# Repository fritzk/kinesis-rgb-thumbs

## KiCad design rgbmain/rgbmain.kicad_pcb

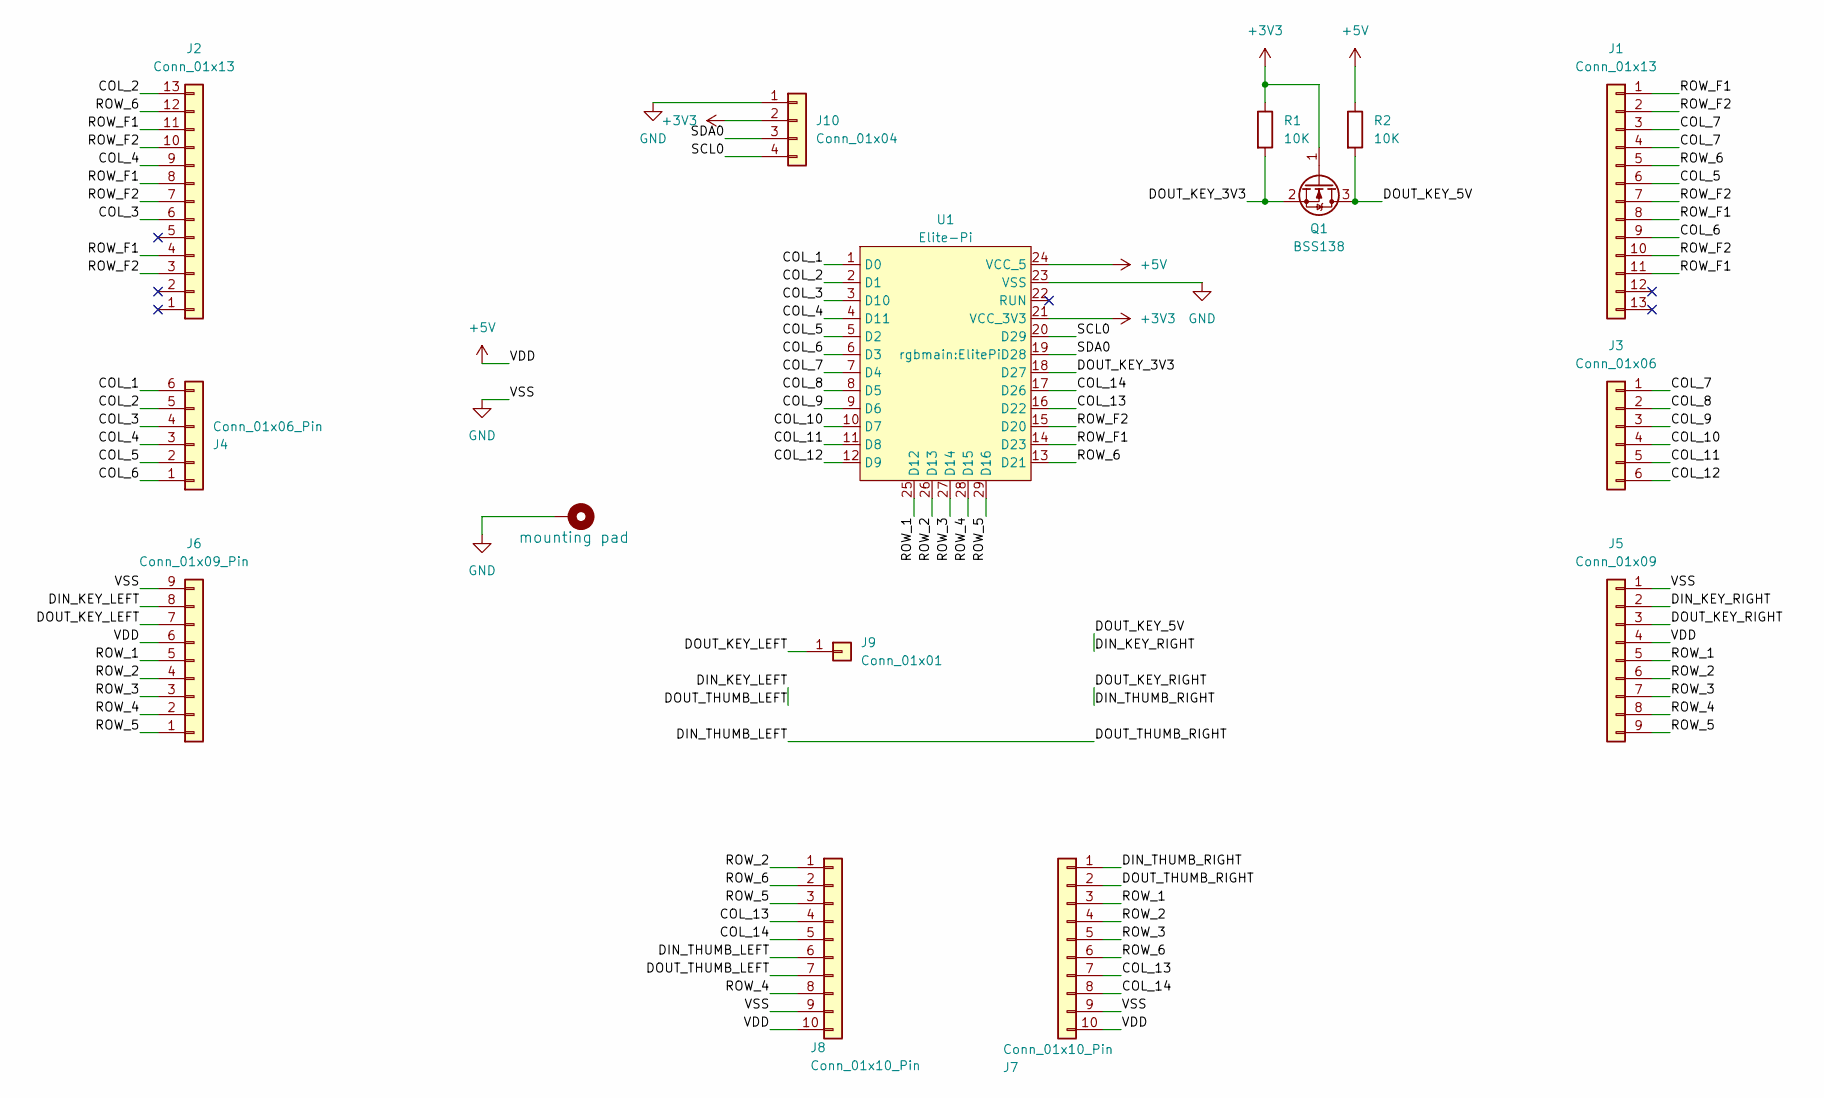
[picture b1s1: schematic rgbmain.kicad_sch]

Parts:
H1: mounting pad; MountingHole_4.3mm_M4_Pad
J1, J2: Conn_01x13; Molex_0039532135
J3: Conn_01x06; Molex_KK-254_AE-6410-06A_1x06_P2.54mm_Vertical
J4: Conn_01x06_Pin; Molex_KK-254_AE-6410-06A_1x06_P2.54mm_Vertical
J5: Conn_01x09; Molex_KK-254_AE-6410-09A_1x09_P2.54mm_Vertical
J6: Conn_01x09_Pin; Molex_KK-254_AE-6410-09A_1x09_P2.54mm_Vertical
J7, J8: Conn_01x10_Pin; PinHeader_1x10_P2.54mm_Vertical
J9: Conn_01x01; PinHeader_1x01_P1.00mm_Vertical
J10: Conn_01x04; PinSocket_1x04_P2.54mm_Vertical
Q1: BSS138; SOT-23
R1, R2: 10K; R_0805_2012Metric_Pad1.20x1.40mm_HandSolder
U1: Elite-Pi; ElitePi

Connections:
+3V3: J10.2, Q1.1 (G), R1.1, U1.21 (VCC_3V3)
+5V: J5.4, J6.6, J7.10, J8.10, R2.1, U1.24 (VCC_5)
/COL_1: J4.6, U1.1 (D0)
/COL_2: J2.13, J4.5, U1.2 (D1)
/COL_3: J2.6, J4.4, U1.3 (D10)
/COL_4: J2.9, J4.3, U1.4 (D11)
/COL_5: J1.6, J4.2, U1.5 (D2)
/COL_6: J1.9, J4.1, U1.6 (D3)
/COL_7: J1.3, J1.4, J3.1, U1.7 (D4)
/COL_8: J3.2, U1.8 (D5)
/COL_9: J3.3, U1.9 (D6)
/COL_10: J3.4, U1.10 (D7)
/COL_11: J3.5, U1.11 (D8)
/COL_12: J3.6, U1.12 (D9)
/COL_13: J7.7, J8.4, U1.16 (D22)
/COL_14: J7.8, J8.5, U1.17 (D26)
/DIN_KEY_LEFT: J6.8, J8.7
/DIN_KEY_RIGHT: J5.2, Q1.3 (D), R2.2
/DIN_THUMB_LEFT: J7.2, J8.6
/DIN_THUMB_RIGHT: J5.3, J7.1
/DOUT_KEY_3V3: Q1.2 (S), R1.2, U1.18 (D27)
/DOUT_KEY_LEFT: J6.7, J9.1
/ROW_1: J5.5, J6.5, J7.3, U1.25 (D12)
/ROW_2: J5.6, J6.4, J7.4, J8.1, U1.26 (D13)
/ROW_3: J5.7, J6.3, J7.5, U1.27 (D14)
/ROW_4: J5.8, J6.2, J8.8, U1.28 (D15)
/ROW_5: J5.9, J6.1, J8.3, U1.29 (D16)
/ROW_6: J1.5, J2.12, J7.6, J8.2, U1.13 (D21)
/ROW_F1: J1.1, J1.8, J1.11, J2.4, J2.8, J2.11, U1.14 (D23)
/ROW_F2: J1.2, J1.7, J1.10, J2.3, J2.7, J2.10, U1.15 (D20)
/SCL0: J10.4, U1.20 (D29)
/SDA0: J10.3, U1.19 (D28)
GND: H1.1, J5.1, J6.9, J7.9, J8.9, J10.1, U1.23 (VSS)

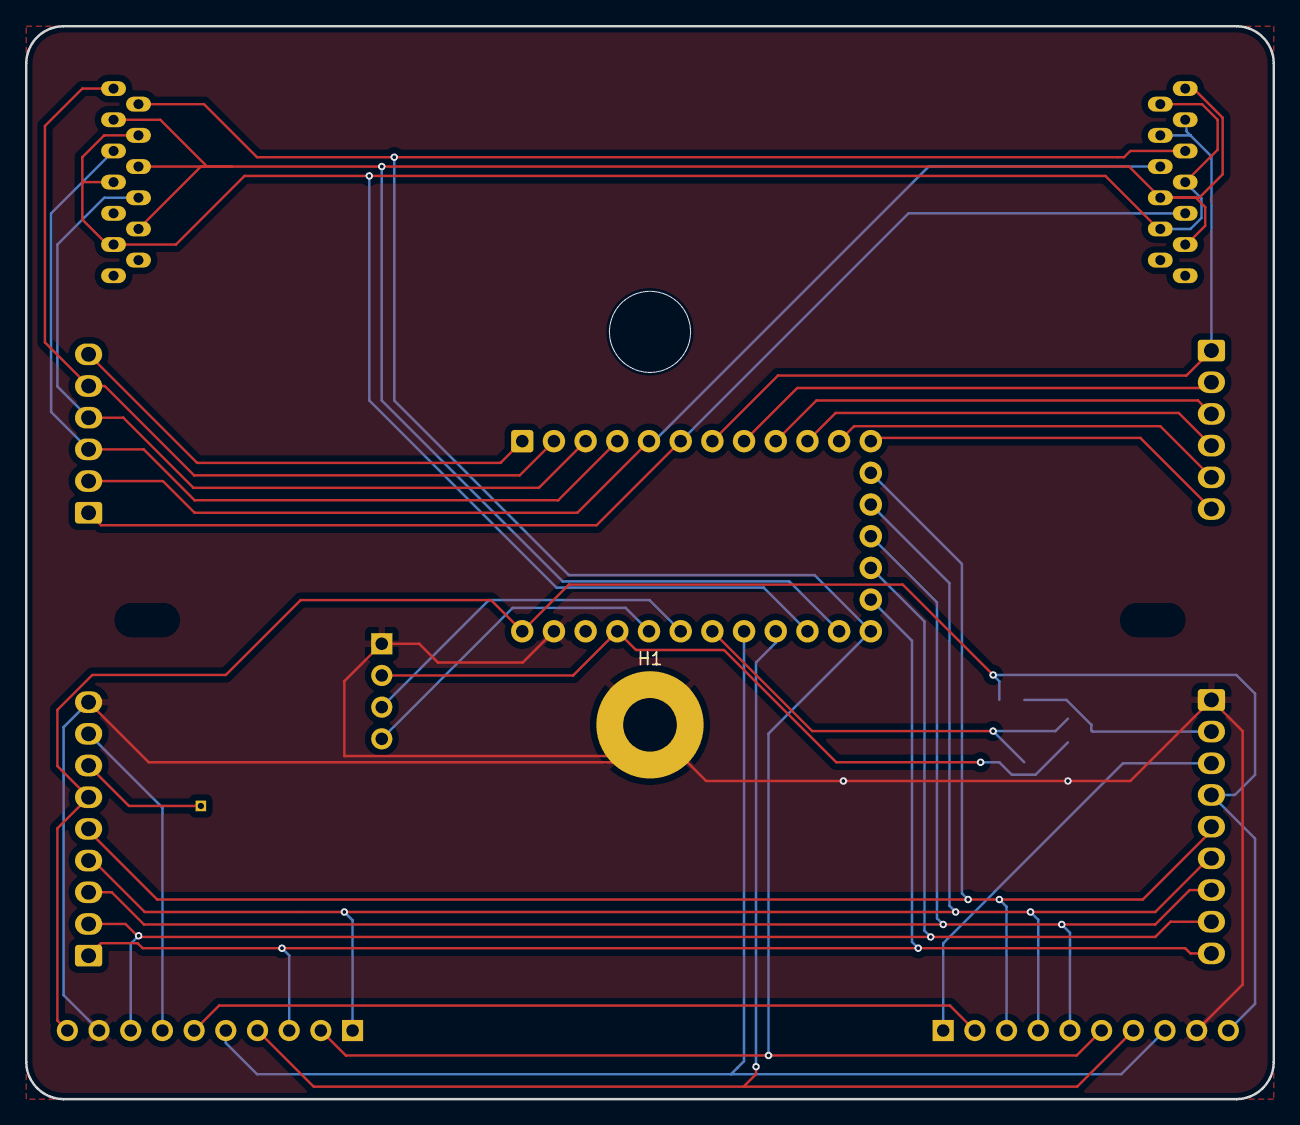
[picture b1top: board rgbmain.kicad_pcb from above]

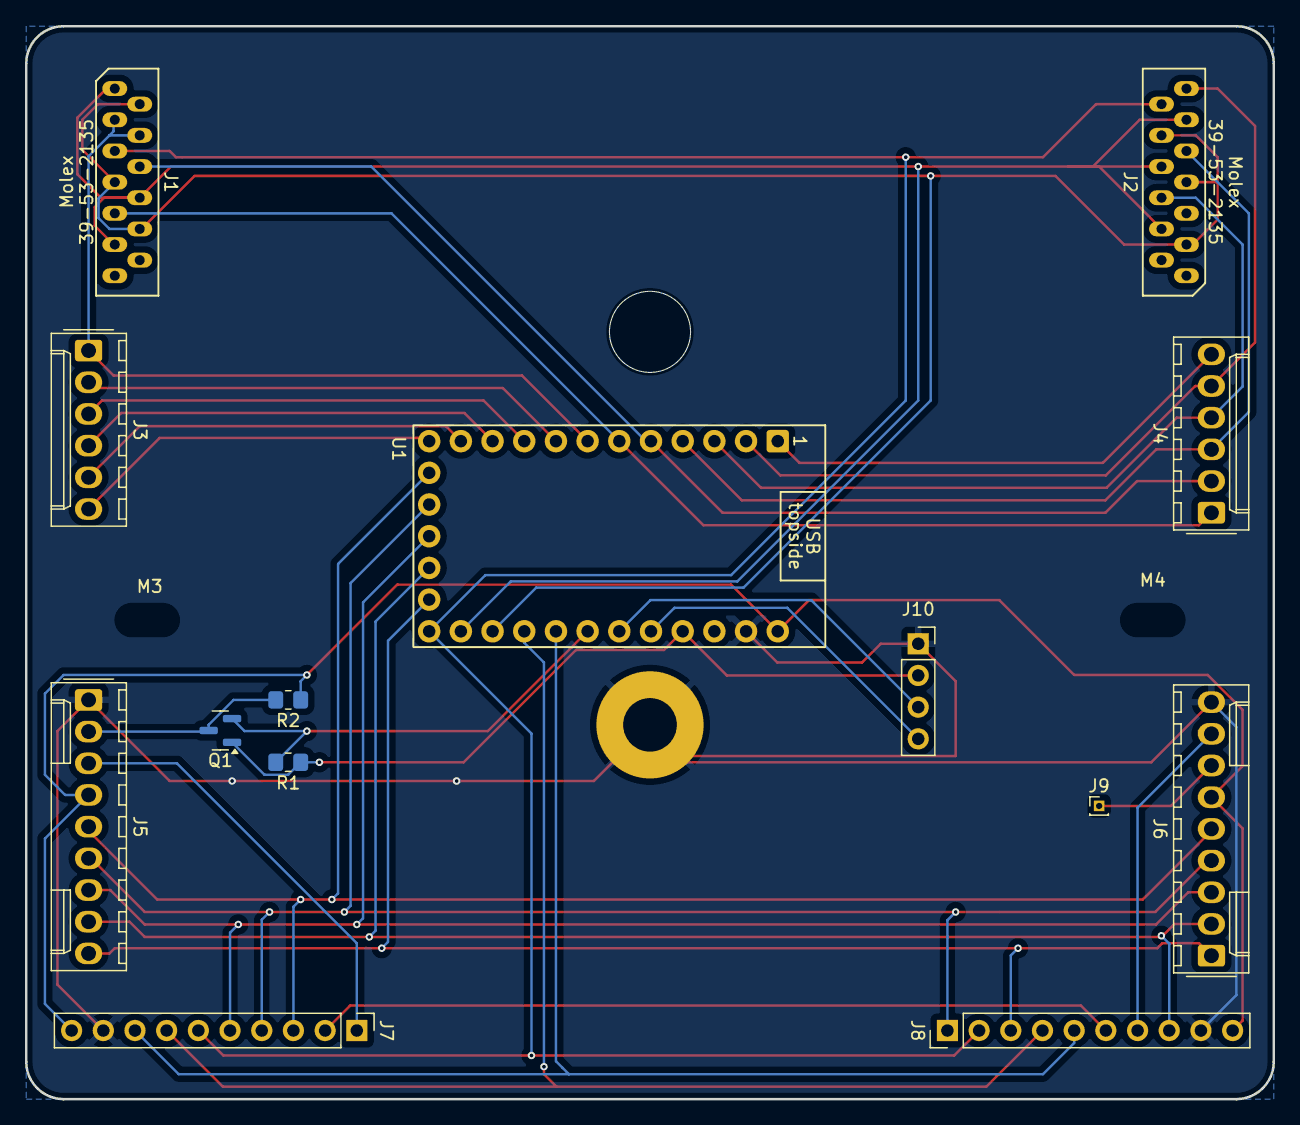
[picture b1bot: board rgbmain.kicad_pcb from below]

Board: 2 copper layers, 100.0 x 86.0 mm, 18 parts (17 on the bottom side), 33 nets.

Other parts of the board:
M1: MountingHole_6.4mm_M6
M3, M4: MountingHole_4.3mm_M4

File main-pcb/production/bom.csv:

Designator,Footprint,Quantity,Value,LCSC Part #
H1,MountingHole_4.3mm_M4_Pad,1,mounting pad,
"J1, J2",Molex_0039532135,2,Conn_01x13,
J10,PinSocket_1x04_P2.54mm_Vertical,1,Conn_01x04,
J3,Molex_KK-254_AE-6410-06A_1x06_P2.54mm_Vertical,1,Conn_01x06,
J4,Molex_KK-254_AE-6410-06A_1x06_P2.54mm_Vertical,1,Conn_01x06_Pin,
J5,Molex_KK-254_AE-6410-09A_1x09_P2.54mm_Vertical,1,Conn_01x09,
J6,Molex_KK-254_AE-6410-09A_1x09_P2.54mm_Vertical,1,Conn_01x09_Pin,
"J7, J8",PinHeader_1x10_P2.54mm_Vertical,2,Conn_01x10_Pin,
J9,PinHeader_1x01_P1.00mm_Vertical,1,Conn_01x01,
M1,MountingHole_6.4mm_M6,1,MountingHole_6.4mm_M6,
Q1,SOT-23,1,BSS138,
"R1, R2",0805,2,10K,
U1,ElitePi,1,Elite-Pi,

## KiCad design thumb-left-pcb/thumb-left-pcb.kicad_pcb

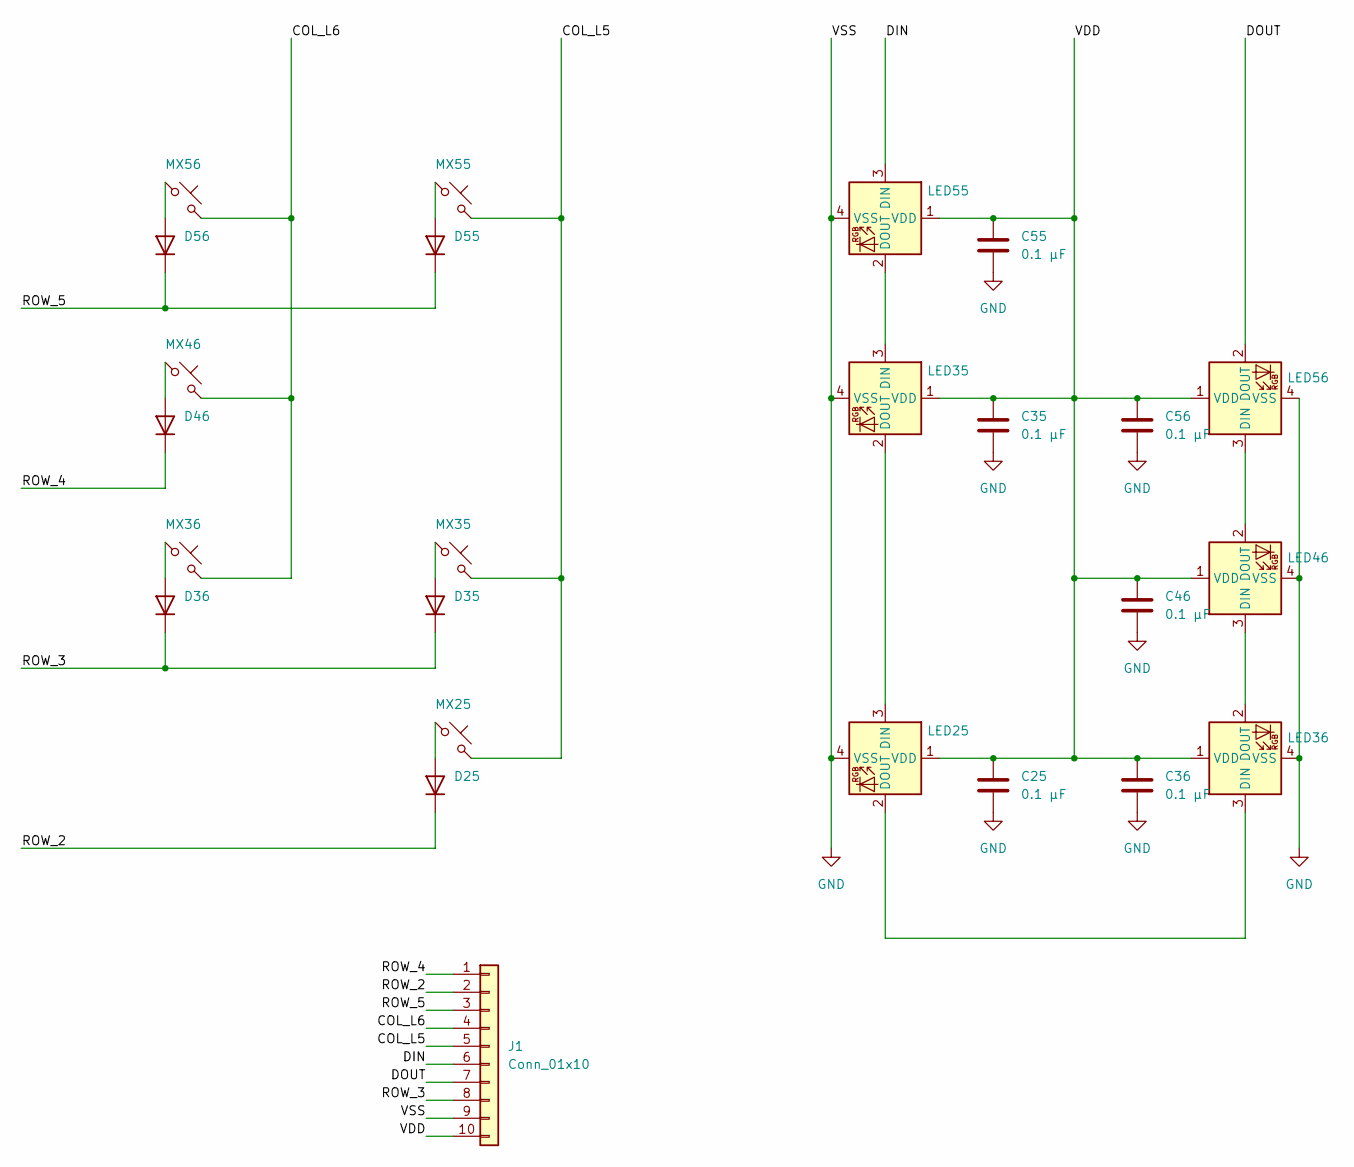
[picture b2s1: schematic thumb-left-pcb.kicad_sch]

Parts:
C25, C35, C36, C46, C55, C56: 0.1 µF; C_0805_2012Metric_Pad1.18x1.45mm_HandSolder
D25, D35, D36, D46, D55, D56: 1N4148WL; D_SOD-123F
J1: Conn_01x10; PinHeader_1x10_P2.54mm_Vertical
LED25, LED35, LED36, LED46, LED55, LED56: MX_SK6812MINI-E; LED_MX_6028R
MX25, MX35, MX55, MX56: MX_SW_HS; SW_Cherry_MX_PCB_1.00u
MX36, MX46: MX_SW_HS; SW_Cherry_MX_PCB_2.00u_90deg

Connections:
/COL_L5: J1.5, MX25.2, MX35.2, MX55.2
/COL_L6: J1.4, MX36.2, MX46.2, MX56.2
/DIN: J1.6, LED55.3 (DIN)
/DOUT: J1.7, LED56.2 (DOUT)
/ROW_2: D25.1 (K), J1.2
/ROW_3: D35.1 (K), D36.1 (K), J1.8
/ROW_4: D46.1 (K), J1.1
/ROW_5: D55.1 (K), D56.1 (K), J1.3
/VDD: C25.1, C35.1, C36.1, C46.1, C55.1, C56.1, J1.10, LED25.1 (VDD), LED35.1 (VDD), LED36.1 (VDD), LED46.1 (VDD), LED55.1 (VDD), LED56.1 (VDD)
GND: C25.2, C35.2, C36.2, C46.2, C55.2, C56.2, J1.9, LED25.4 (VSS), LED35.4 (VSS), LED36.4 (VSS), LED46.4 (VSS), LED55.4 (VSS), LED56.4 (VSS)
unnamed: D25.2 (A), MX25.1
unnamed: D35.2 (A), MX35.1
unnamed: D36.2 (A), MX36.1
unnamed: D46.2 (A), MX46.1
unnamed: D55.2 (A), MX55.1
unnamed: D56.2 (A), MX56.1
unnamed: LED25.3 (DIN), LED35.2 (DOUT)
unnamed: LED25.2 (DOUT), LED36.3 (DIN)
unnamed: LED35.3 (DIN), LED55.2 (DOUT)
unnamed: LED36.2 (DOUT), LED46.3 (DIN)
unnamed: LED46.2 (DOUT), LED56.3 (DIN)

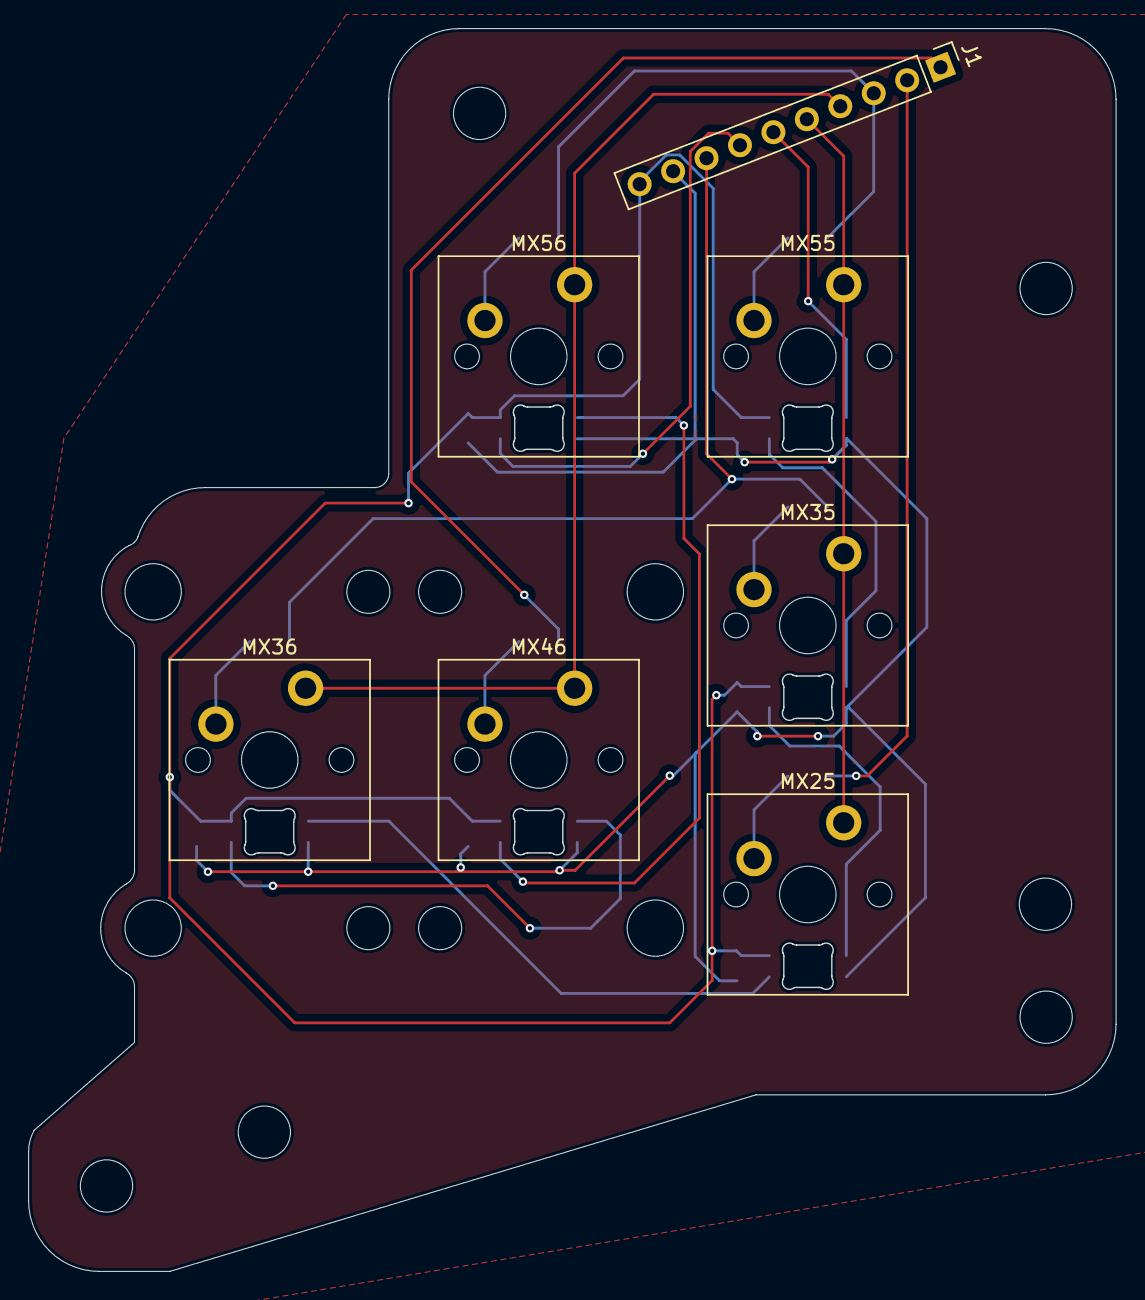
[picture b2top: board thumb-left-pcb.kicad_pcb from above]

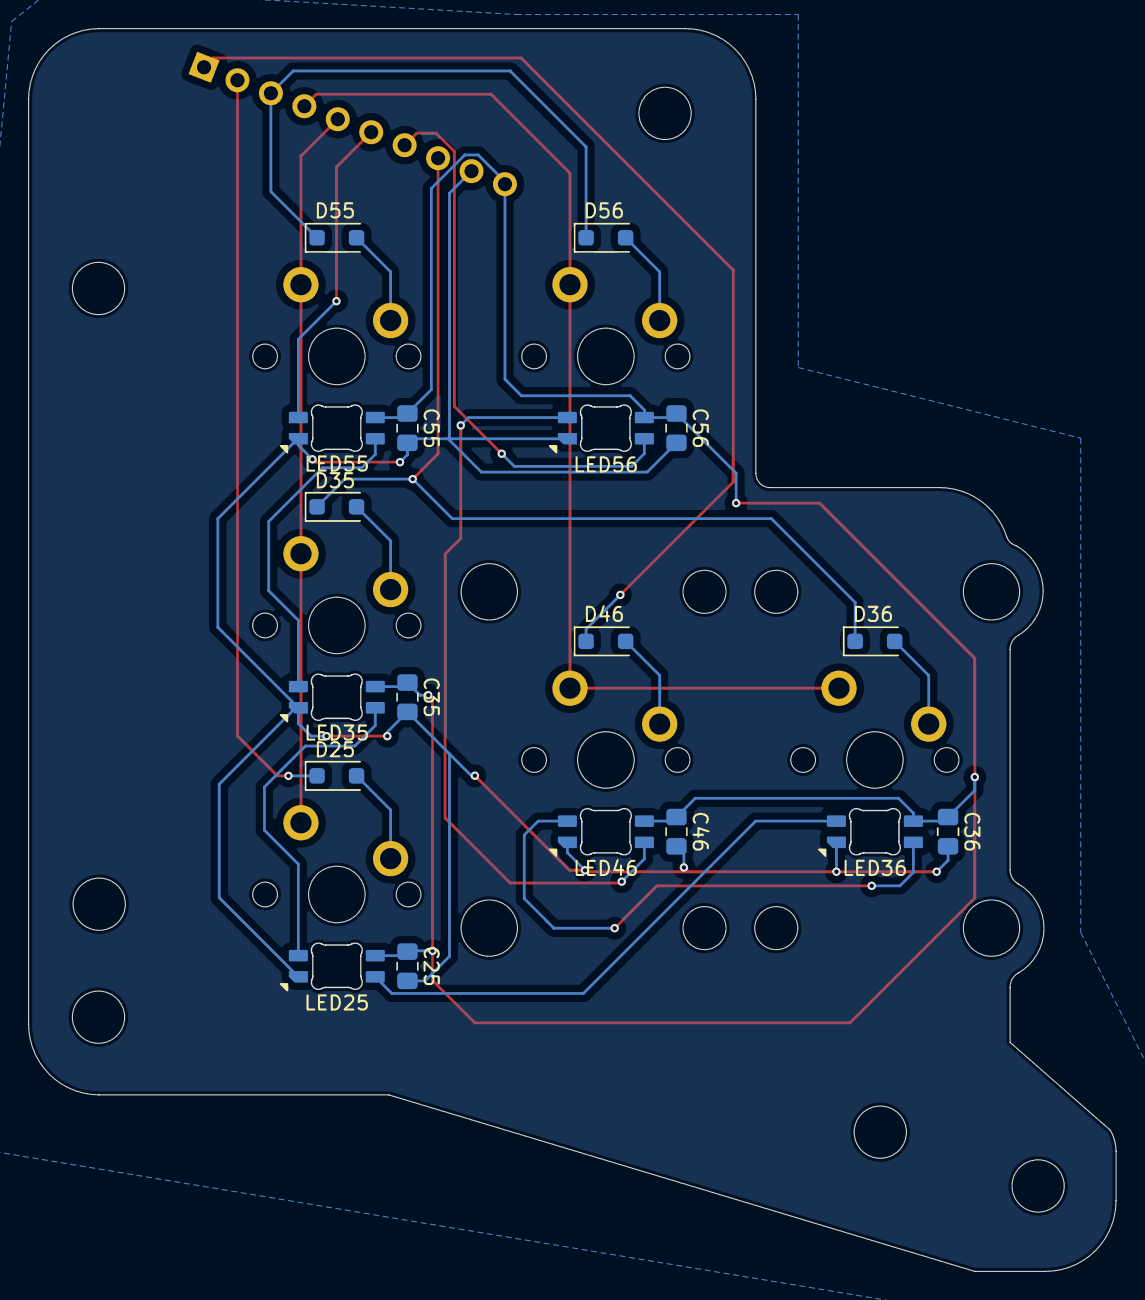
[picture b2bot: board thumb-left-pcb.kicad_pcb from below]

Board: 2 copper layers, 76.9 x 88.0 mm, 31 parts (18 on the bottom side), 21 nets.

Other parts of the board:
REF1, REF2, REF3, REF4, REF5, REF6: MountingHole_3.7mm

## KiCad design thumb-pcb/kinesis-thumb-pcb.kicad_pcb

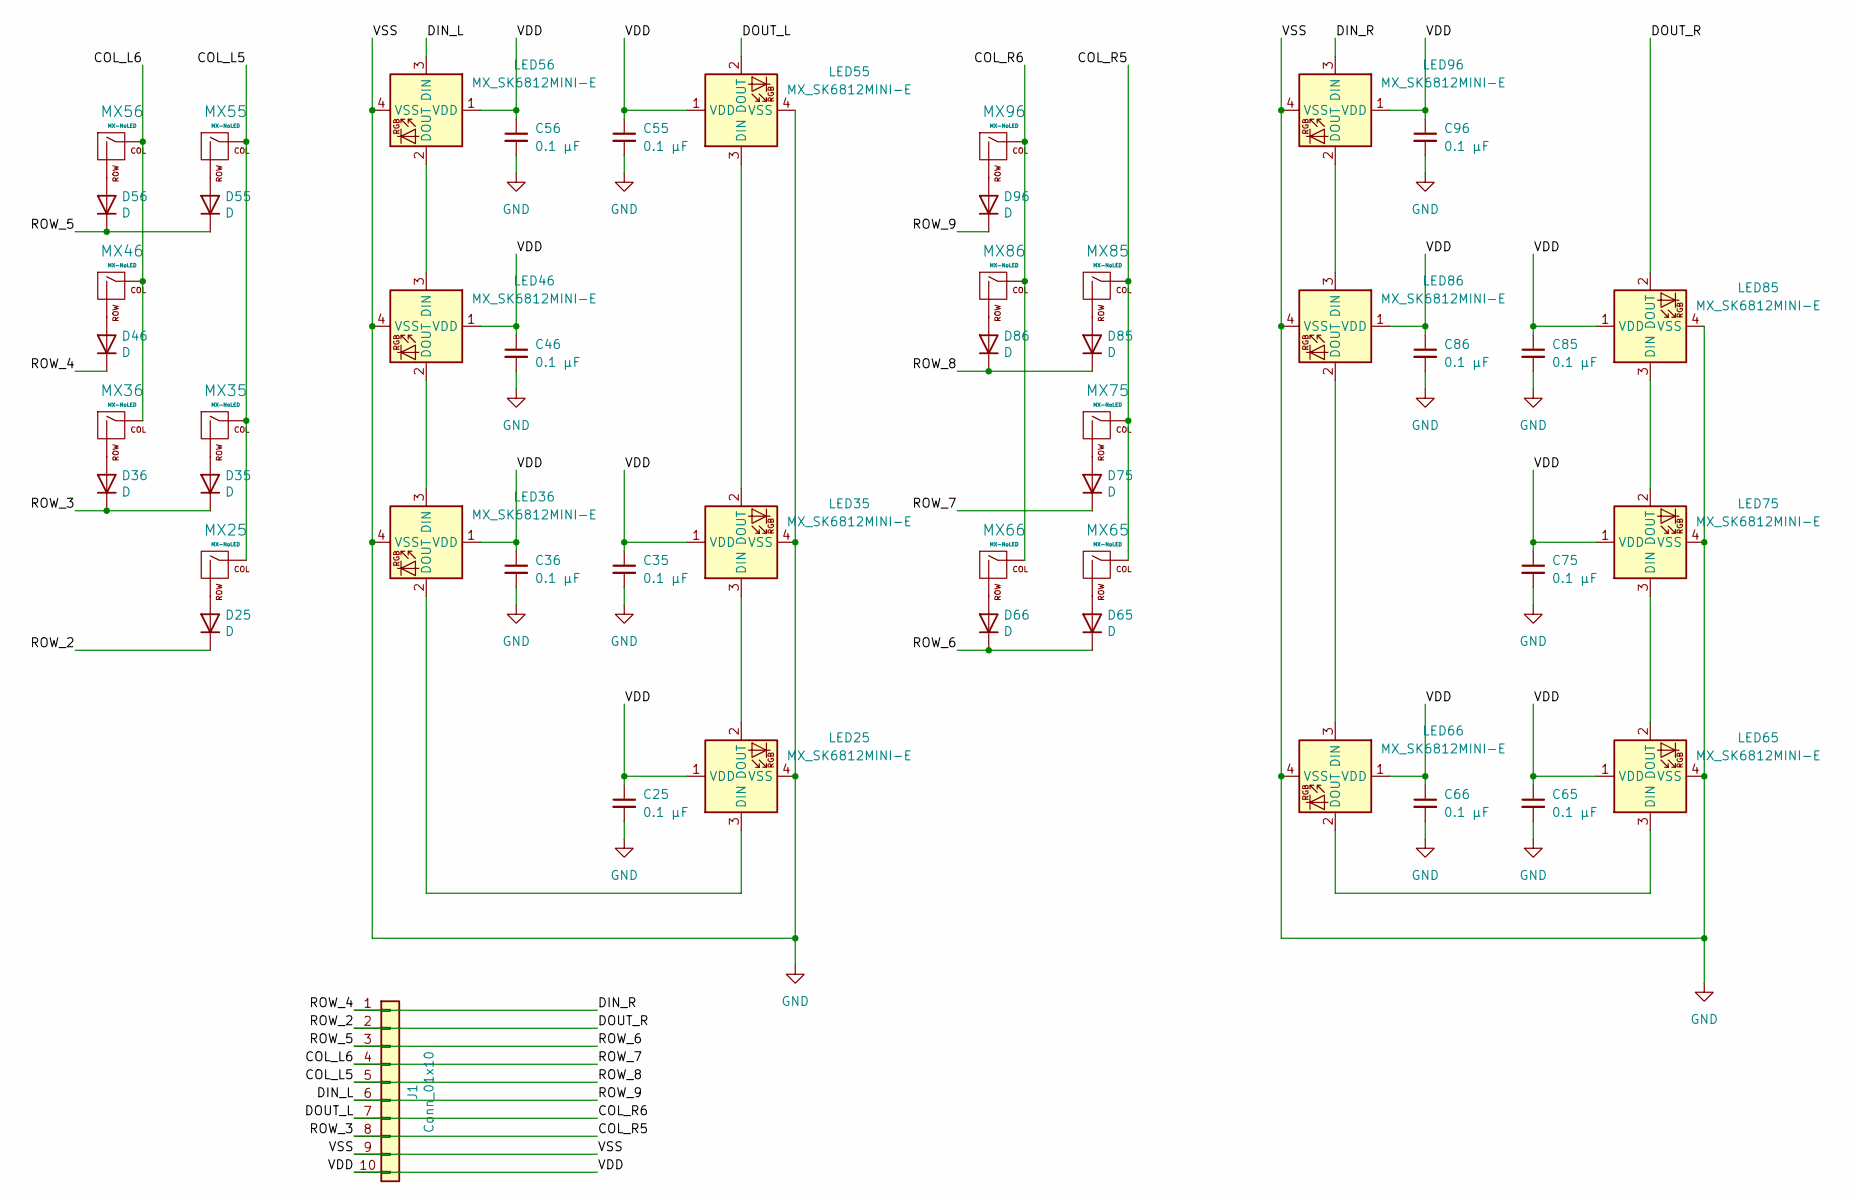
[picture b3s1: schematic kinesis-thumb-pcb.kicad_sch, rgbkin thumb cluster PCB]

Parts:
C25, C35, C36, C46, C55, C56, C65, C66, C75, C85, C86, C96: 0.1 µF; C_0805_2012Metric_Pad1.18x1.45mm_HandSolder
D25, D35, D36, D46, D55, D56, D65, D66, D75, D85, D86, D96: D; D_SOD-323_HandSoldering
J1: Conn_01x10; Pin_Header_Straight_1x10_Pitch2.54mm
LED25, LED35, LED36, LED46, LED55, LED56, LED65, LED66, LED75, LED85, LED86, LED96: MX_SK6812MINI-E; LED_MX_6028R
MX25, MX35, MX36, MX46, MX55, MX56, MX65, MX66, MX75, MX85, MX86, MX96: MX-NoLED

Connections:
/COL_L5: D85.1 (K), D86.1 (K), J1.5, MX25.1 (COL), MX35.1 (COL), MX55.1 (COL)
/COL_L6: D75.1 (K), J1.4, MX36.1 (COL), MX46.1 (COL), MX56.1 (COL)
/COL_R5: D35.1 (K), D36.1 (K), J1.8, MX65.1 (COL), MX75.1 (COL), MX85.1 (COL)
/COL_R6: J1.7, LED55.2 (DOUT), MX66.1 (COL), MX86.1 (COL), MX96.1 (COL)
/DIN_L: D96.1 (K), J1.6, LED56.3 (DIN)
/DIN_R: D46.1 (K), J1.1, LED96.3 (DIN)
/DOUT_R: D25.1 (K), J1.2, LED85.2 (DOUT)
/ROW_5: D55.1 (K), D56.1 (K), D65.1 (K), D66.1 (K), J1.3
/VDD: C25.1, C35.1, C36.1, C46.1, C55.1, C56.1, C65.1, C66.1, C75.1, C85.1, C86.1, C96.1, J1.10, LED25.1 (VDD), LED35.1 (VDD), LED36.1 (VDD), LED46.1 (VDD), LED55.1 (VDD), LED56.1 (VDD), LED65.1 (VDD), LED66.1 (VDD), LED75.1 (VDD), LED85.1 (VDD), LED86.1 (VDD), LED96.1 (VDD)
GND: C25.2, C35.2, C36.2, C46.2, C55.2, C56.2, C65.2, C66.2, C75.2, C85.2, C86.2, C96.2, J1.9, LED25.4 (VSS), LED35.4 (VSS), LED36.4 (VSS), LED46.4 (VSS), LED55.4 (VSS), LED56.4 (VSS), LED65.4 (VSS), LED66.4 (VSS), LED75.4 (VSS), LED85.4 (VSS), LED86.4 (VSS), LED96.4 (VSS)
unnamed: D25.2 (A), MX25.2 (ROW)
unnamed: D35.2 (A), MX35.2 (ROW)
unnamed: D36.2 (A), MX36.2 (ROW)
unnamed: D46.2 (A), MX46.2 (ROW)
unnamed: D55.2 (A), MX55.2 (ROW)
unnamed: D56.2 (A), MX56.2 (ROW)
unnamed: D65.2 (A), MX65.2 (ROW)
unnamed: D66.2 (A), MX66.2 (ROW)
unnamed: D75.2 (A), MX75.2 (ROW)
unnamed: D85.2 (A), MX85.2 (ROW)
unnamed: D86.2 (A), MX86.2 (ROW)
unnamed: D96.2 (A), MX96.2 (ROW)
unnamed: LED25.3 (DIN), LED36.2 (DOUT)
unnamed: LED25.2 (DOUT), LED35.3 (DIN)
unnamed: LED35.2 (DOUT), LED55.3 (DIN)
unnamed: LED36.3 (DIN), LED46.2 (DOUT)
unnamed: LED46.3 (DIN), LED56.2 (DOUT)
unnamed: LED65.3 (DIN), LED66.2 (DOUT)
unnamed: LED65.2 (DOUT), LED75.3 (DIN)
unnamed: LED66.3 (DIN), LED86.2 (DOUT)
unnamed: LED75.2 (DOUT), LED85.3 (DIN)
unnamed: LED86.3 (DIN), LED96.2 (DOUT)

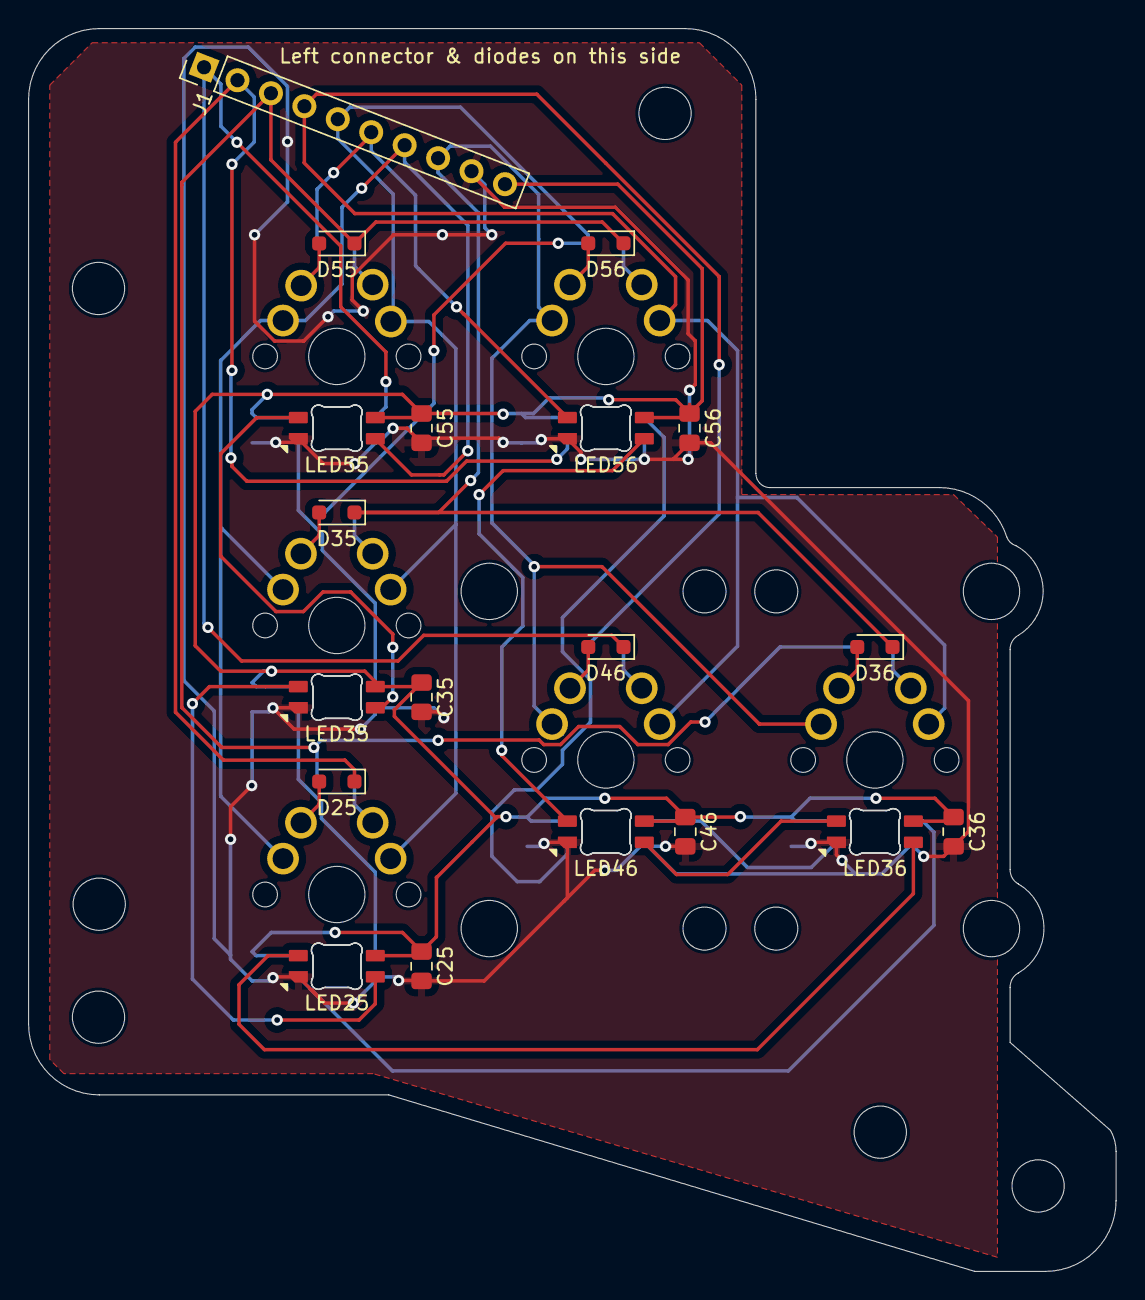
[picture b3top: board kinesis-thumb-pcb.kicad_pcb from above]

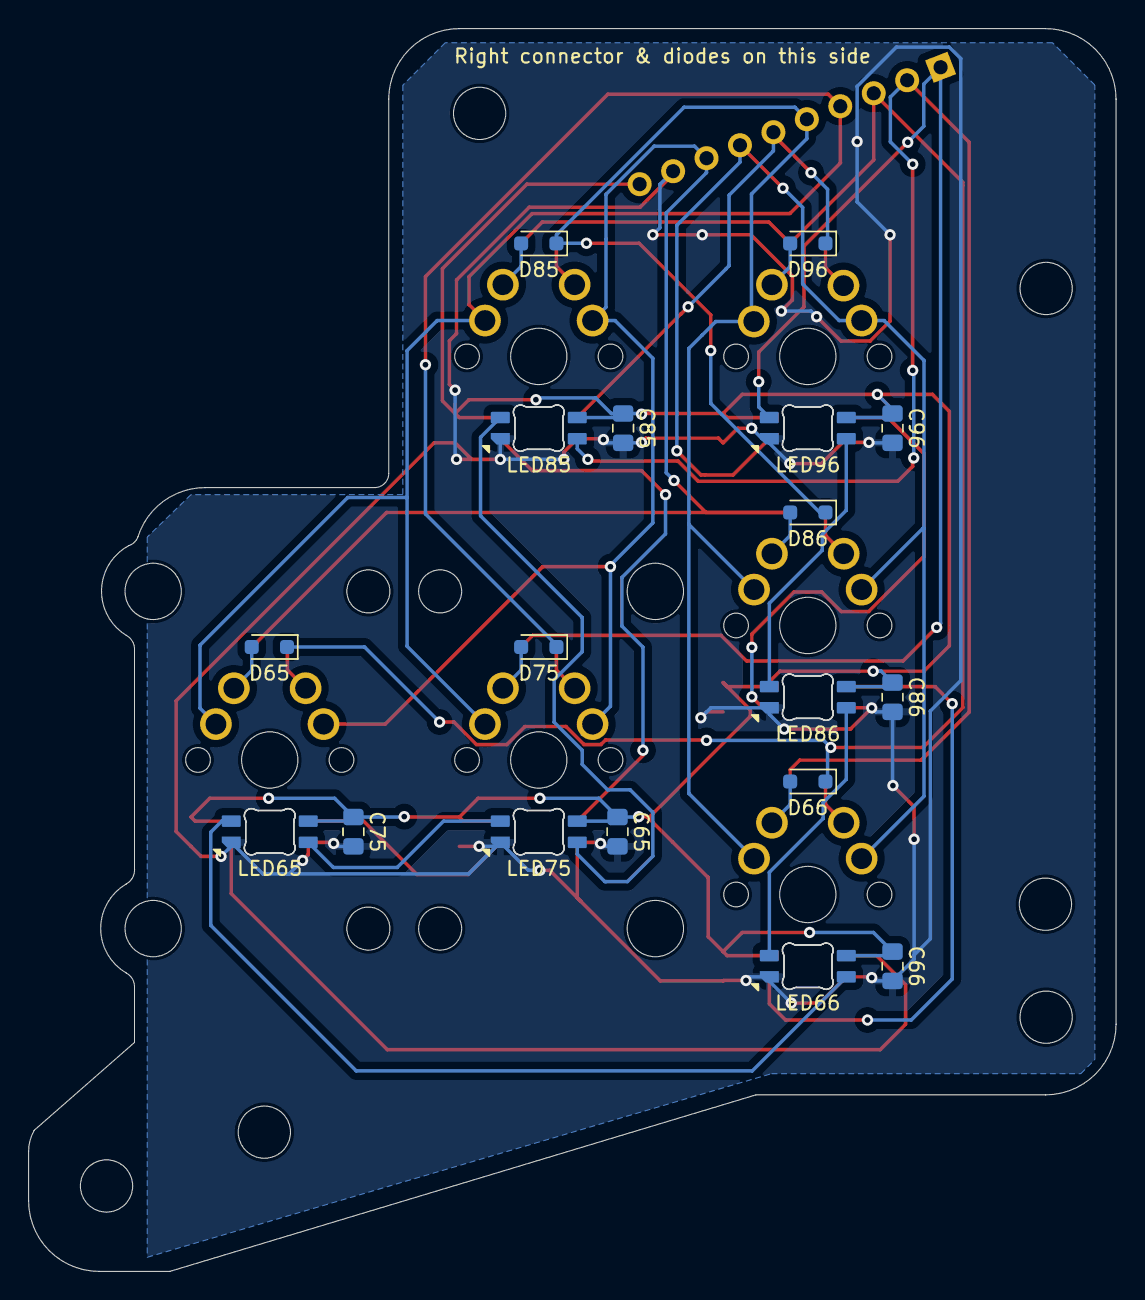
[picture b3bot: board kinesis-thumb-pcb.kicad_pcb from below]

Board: 2 copper layers, 76.9 x 88.0 mm, 55 parts (30 on the bottom side), 32 nets.

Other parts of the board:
REF1, REF2, REF3, REF4, REF5, REF6: MountingHole_3.7mm

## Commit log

2025-05-26 Start of per key pcb
2025-05-26 Schematics for per key pcb done
2025-05-26 First attempt at layout. Not good.
    Pins are too close together and won't fit on board.
2025-05-27 Routed, but DRC violation
2025-05-31 Passing all DRC
2025-05-31 Smaller board
2025-05-31 Ground fill
2025-05-31 Passing JLCPCB rules (but some warnings)
2025-05-31 Gerber creation options
2025-08-30 Imported from https://github.com/dcpedit/pillzmod
2025-08-30 MX_Alps_Hybrid submodule
2025-08-31 Part placement
2025-08-31 Checkpoint - routing
2025-08-31 SOD123 Diodes
2025-08-31 Routed
2025-08-31 Fully routed
2025-09-15 checkpoint
2025-09-15 Left/Right thumb clusters
    Split left and right instead of sharing one pcb.
2025-09-17 Schematic for L/R thumb
    Imported from github.com/dcpedit/pillzmod
2025-09-17 Component layout
2025-09-17 Fill all zones
2025-09-17 Ignore temporary/local kicad files
2025-09-17 Update capacitor footprint
    Use the hand solder pads.
2025-09-17 Update silk for DRC
2025-09-17 Update footprints
2025-09-17 Switch and diodes fully routed
2025-09-17 Updated design rules
    JLPCB rules + pad to edge for led cutouts
2025-09-17 Update ignore
2025-09-17 left thumb starting pcb
    Copy in right and flip.
2025-09-17 update left footprints
2025-09-17 rework left-thumb schematic
    The uuid's match up so that when the pcb is layed out
    the right can be used as a starting point.
2025-09-17 sync left schematic with pcb
2025-09-17 move components to correct side
2025-09-17 update copper edge clearance for left pcb
2025-09-17 left complete with fill
2025-09-18 added 2u stabilizers
2025-09-18 left D25 flipped
2025-09-18 fixed net names for left thumb columns
2025-09-18 fix left thumb nets
2025-09-18 left thumb routed
2025-10-12 README.md
2025-10-13 remove key-pcb
    moved to it's own repo
2025-10-18 initialize kicad
2025-10-18 initial pin labeling
2025-10-19 right side connectors were rotated incorrectly
2025-10-19 add a license, why not CERN
2025-10-19 symbol for Elite-Pi added
2025-10-19 wire mcu up
2025-10-22 elite-pi footprint
2025-10-22 changed number to match footprint
2025-10-22 molex function key header
    copied from: https://github.com/dcpedit/pillzmod/blob/main/pcb-pro/kinesisMod_board_connectors.pretty/Molex_0039532135.kicad_mod
2025-10-22 footprints added
2025-10-22 use the Molex KK *2.54*
    footprints sourced from: https://github.com/SnowMB/pcb_library
2025-10-22 use vertical pcb connectors
    horizontal take up too much board space
2025-10-22 initial pcb placement
2025-10-26 wired up all function keys
2025-10-26 pcb layout complete
2025-10-27 changed thumb connectors
    wanted thumbs to be the same as stock.
2025-10-27 more connector flipping
2025-10-28 sent out for fabrication
2025-10-28 prepare main for single repo
2025-10-28 .gitignore
2025-10-28 prepare key for single repo
2025-10-28 normalize names
2025-10-28 apply LICENSE to all
